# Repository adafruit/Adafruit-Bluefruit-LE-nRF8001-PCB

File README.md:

## Bluefruit LE - Bluetooth Low Energy (BLE 4.0) - nRF8001 Breakout - v1.0 PCB
<a href="http://www.adafruit.com/products/1697"><br/>
Click here to purchase one from the Adafruit shop</a>

Our Adafruit Bluefruit LE (Bluetooth Smart, Bluetooth Low Energy, Bluetooth 4.0) nRF8001 Breakout allows you to establish an easy to use wireless link between your Arduino and any compatible iOS or Android (4.3+) device. It works by simulating a UART device beneath the surface, sending ASCII data back and forth between the devices, letting you decide what data to send and what to do with it on either end of the connection.

Unlike classic Bluetooth, BLE has no big contracts to sign and no major hoops that you have to jump through to create iOS peripherals that you can legally design and distribute in the App Store, which makes it a great choice compared to classic Bluetooth which had (and still has) a lot of restrictions around it on the iOS platform.

These are the PCB files for Adafruit Bluefruit LE nRF8001 PCB. The format is EagleCAD schematic and board layout
- https://www.adafruit.com/product/1697

### License

Adafruit invests time and resources providing this open source design, please support Adafruit and open-source hardware by purchasing products from [Adafruit](https://www.adafruit.com)!

All text above must be included in any redistribution

Designed by Limor Fried/Ladyada for Adafruit Industries.
Creative Commons Attribution/Share-Alike, all text above must be included in any redistribution. 
See license.txt for additional information.

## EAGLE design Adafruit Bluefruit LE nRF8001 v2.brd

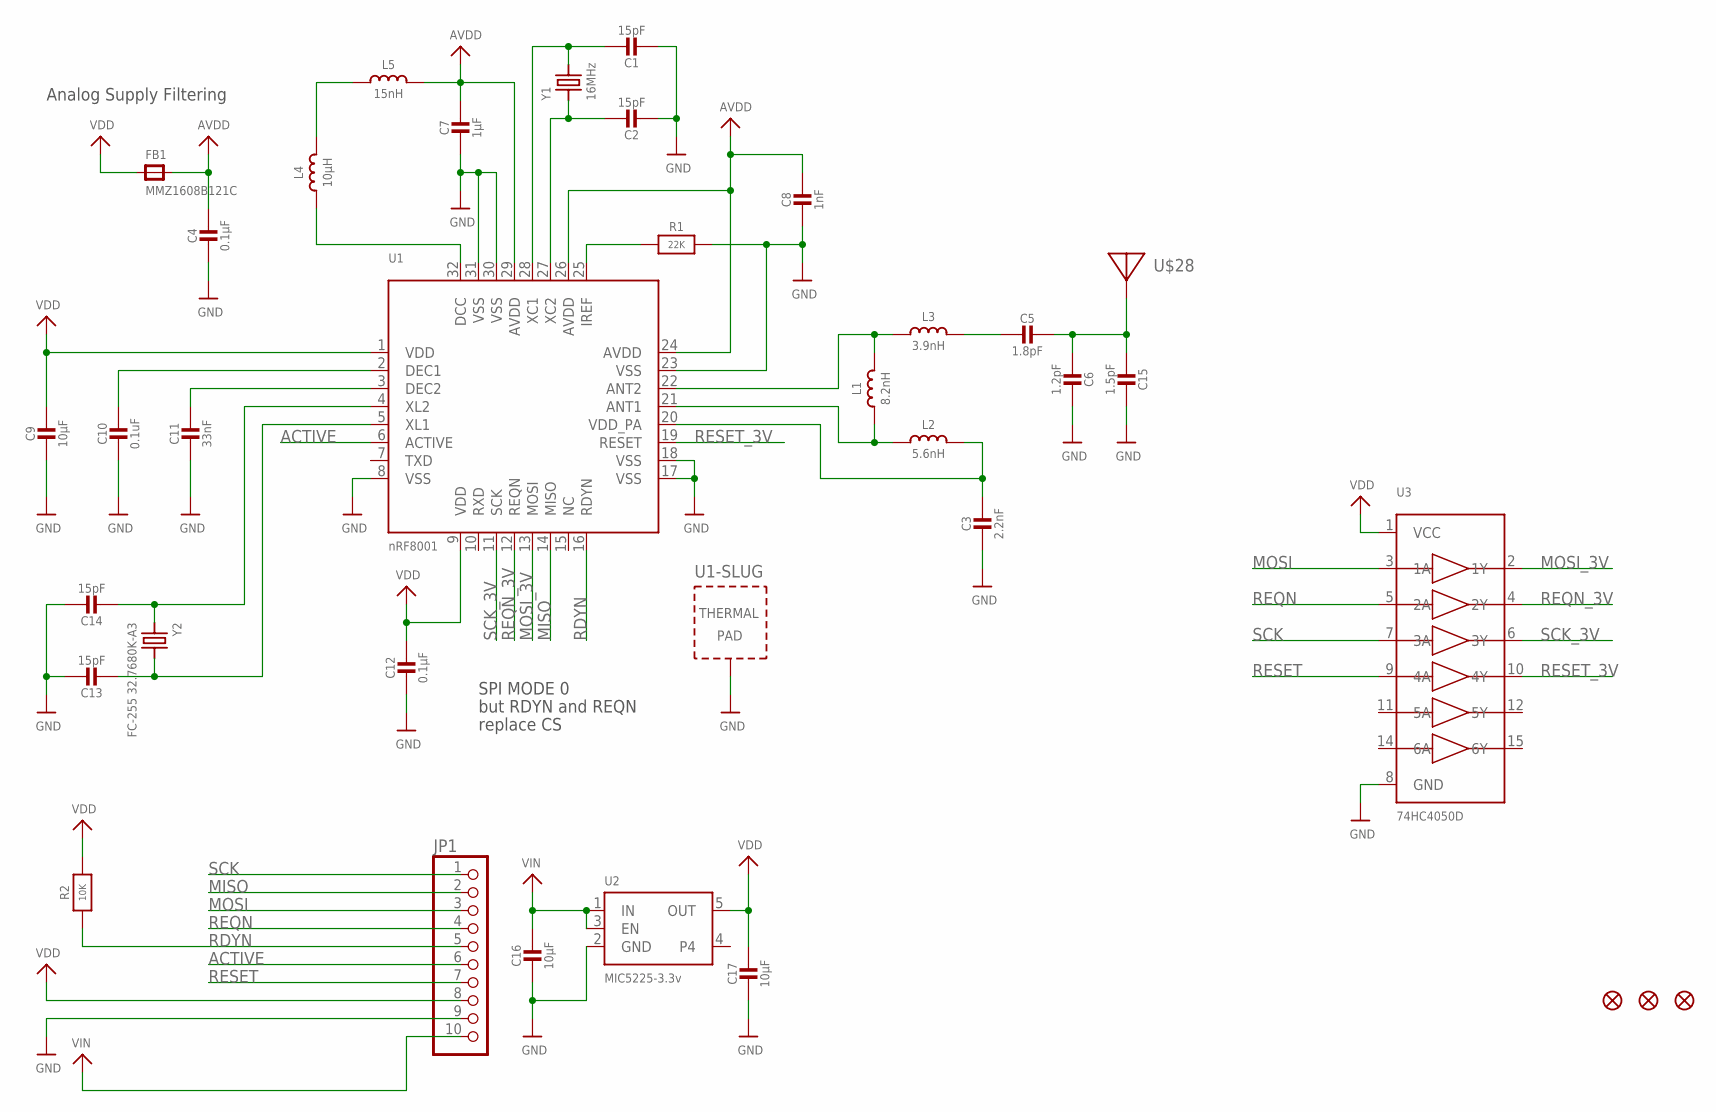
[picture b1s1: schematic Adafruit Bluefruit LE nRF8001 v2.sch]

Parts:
C1, C2, C13, C14: 15pF; 0805-NO
C3: 2.2nF; _0402
C4, C12: 0.1µF; 0805-NO
C5: 1.8pF; _0402MP
C6: 1.2pF; _0402MP
C7: 1µF; 0805-NO
C8: 1nF; _0603
C9, C16, C17: 10µF; 0805-NO
C10: 0.1uF; 0805-NO
C11: 33nF; 0805-NO
C15: 1.5pF; _0402MP
FB1: MMZ1608B121C; 0805
FID1, FID2, FID3: FIDUCIAL""; FIDUCIAL_1MM
JP1: HEADER-1X1070MIL; 1X10_ROUND70
L1: 8.2nH; _0402
L2: 5.6nH; _0402
L3: 3.9nH; _0402
L4: 10µH; _0603
L5: 15nH; _0603
R1: 22K; _0805MP
R2: 10K; 0805-NO
U1: nRF8001; QFN32_5MM
U2: MIC5225-3.3v; SOT23-5
U3: 74HC4050D; TSSOP16
U$28: ANTENNA_PCBNRF8001_1.6MM; ANT_PCB_2.4GHZ_NRF8001_1.6MM_1OZ
Y1: 16MHz; CRYSTAL_3.2X2.5
Y2: FC-255 32.7680K-A3; CRYSTAL_8X3.8

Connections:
+3.3V: C9.1, C12.1, C17.1, FB1.1, JP1.8, R2.2, U1.1 (VDD), U1.9 (VDD), U2.5 (OUT), U3.1 (VCC)
ACTIVE: JP1.6, U1.6 (ACTIVE)
AVDD: C4.1, C7.1, C8.1, FB1.2, L5.2, U1.24 (AVDD), U1.26 (AVDD), U1.29 (AVDD)
GND: C1.2, C2.2, C3.2, C4.2, C6.1, C7.2, C8.2, C9.2, C10.2, C11.2, C12.2, C13.1, C14.1, C15.1, C16.2, C17.2, JP1.9, R1.2, U1.8 (VSS), U1.17 (VSS), U1.18 (VSS), U1.23 (VSS), U1.30 (VSS), U1.31 (VSS), U1.33 (TP), U2.2 (GND), U3.8 (GND)
MISO: JP1.2, U1.14 (MISO)
MOSI: JP1.3, U3.3 (1A)
MOSI_3V: U1.13 (MOSI), U3.2 (1Y)
unnamed: L1.2, L3.1, U1.22 (ANT2)
unnamed: L1.1, L2.1, U1.21 (ANT1)
unnamed: C3.1, L2.2, U1.20 (VDD_PA)
unnamed: L4.2, L5.1
unnamed: C5.2, L3.2
unnamed: C11.1, U1.3 (DEC2)
unnamed: C10.1, U1.2 (DEC1)
unnamed: C1.1, U1.28 (XC1), Y1.2
unnamed: C2.1, U1.27 (XC2), Y1.1
unnamed: L4.1, U1.32 (DCC)
unnamed: R1.1, U1.25 (IREF)
unnamed: C5.1, C6.2, C15.2, U$28.FEED
unnamed: C14.2, U1.4 (XL2), Y2.P$1 (1)
unnamed: C13.2, U1.5 (XL1), Y2.P$4 (2)
RDYN: JP1.5, R2.1, U1.16 (RDYN)
REQN: JP1.4, U3.5 (2A)
REQN_3V: U1.12 (REQN), U3.4 (2Y)
RESET: JP1.7, U3.9 (4A)
RESET_3V: U1.19 (RESET), U3.10 (4Y)
SCK: JP1.1, U3.7 (3A)
SCK_3V: U1.11 (SCK), U3.6 (3Y)
VIN: C16.1, JP1.10, U2.1 (IN), U2.3 (EN)

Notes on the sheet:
Analog Supply Filtering
SPI MODE 0
but RDYN and REQN
replace CS

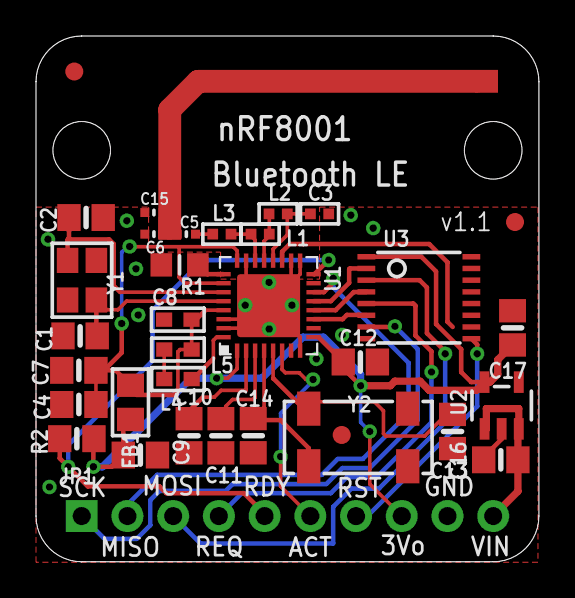
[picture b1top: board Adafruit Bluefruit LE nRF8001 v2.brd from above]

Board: 2 copper layers, 27.9 x 29.2 mm, 36 parts (1 on the bottom side), 29 nets.

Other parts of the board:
U$22: ADAFRUIT_TEXT_20MM

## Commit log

2014-04-15 filez
2014-04-15 reeedme url
2016-09-22 added respin

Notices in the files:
parts and their libraries:
microbuilder: This work is placed in the public domain, and may be freely used for commercial and non-commercial work with the following conditions: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
